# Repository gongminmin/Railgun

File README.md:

# Railgun

A railgun is a type of mass driver. It contains a pair of rails to accelerate a conductor projectile to a high velocity. This project is a design of a toy level railgun. We'd like to make it easy to implement, so people can build it as a hobby project.

NOTE: Please turn on git LFS when cloning this project.

## Design

The principle of our design, and a detailed introduction of subsystems are in [Design](Doc/Design.md)

## Disclaimer

A railgun is operated by **LETHALLY** high voltage and current. If you don't have enough knowledge and experiences on high voltage electric, please keep extreme cautions on insulation.

## Directories

* Circuit folder is the electric design of the system. The files can be open by [KiCad](https://kicad-pcb.org/)
* Doc folder contains some documents

## License

Railgun is distributed under the terms of MIT License. See [LICENSE](LICENSE) for details.

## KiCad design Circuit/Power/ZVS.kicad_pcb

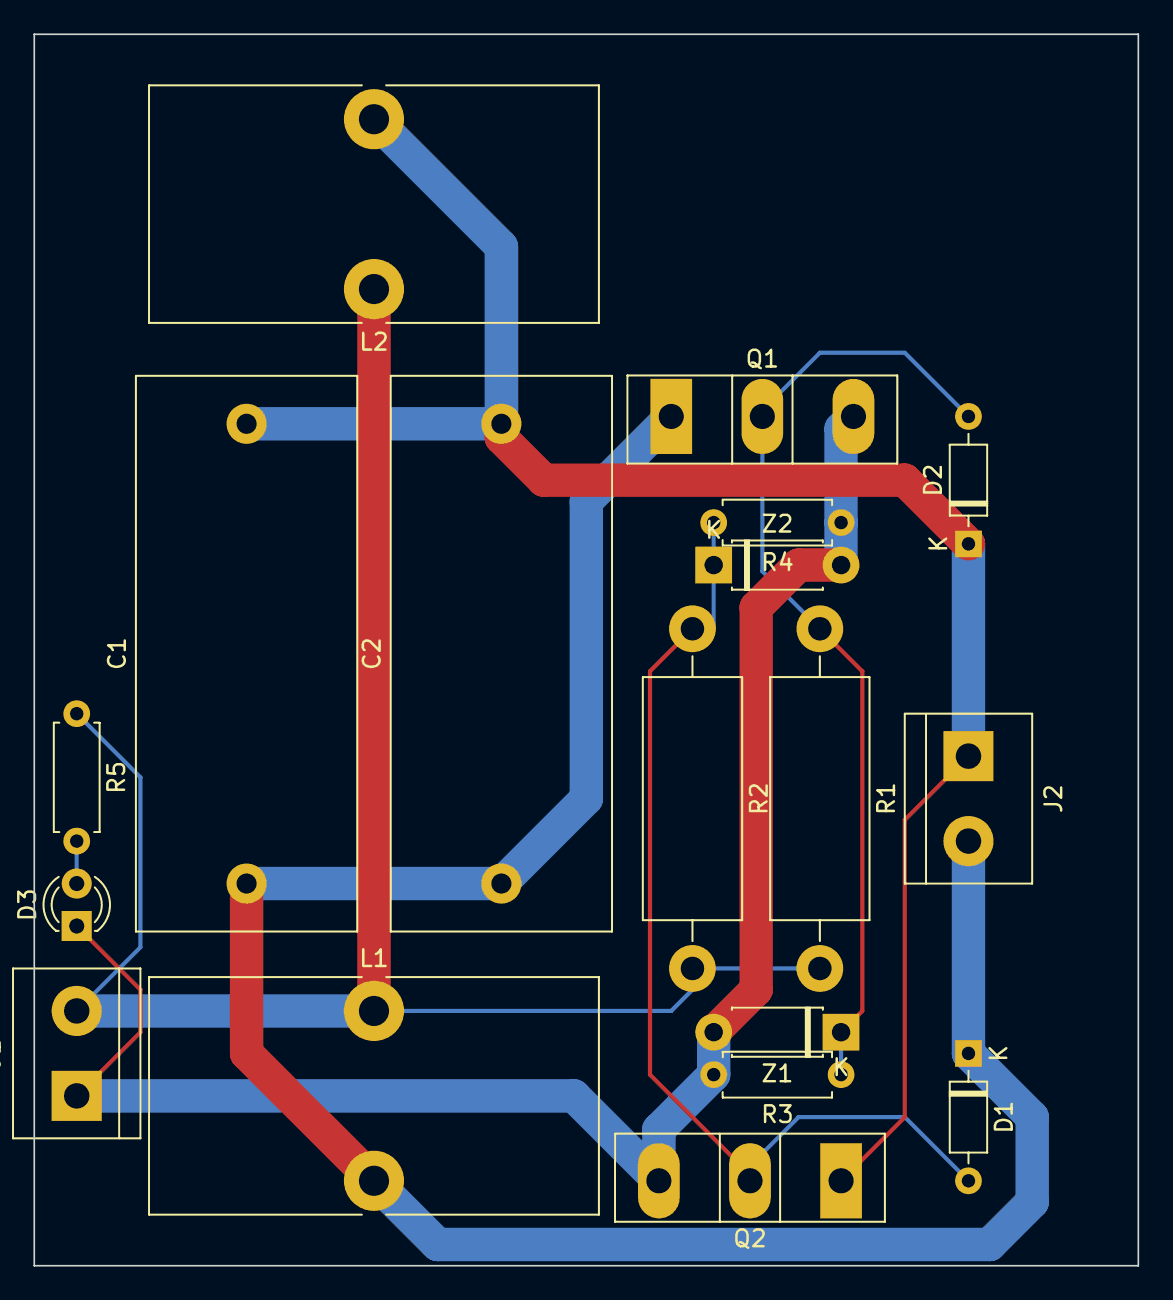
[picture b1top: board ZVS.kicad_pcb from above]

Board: 2 copper layers, 66.0 x 73.7 mm, 18 parts (0 on the bottom side), 7 nets.

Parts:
C1, C2: MKP 0.33uF; C_Rect_L33.0mm_W13.0mm_P27.50mm_MKS4
D1, D2: FR107; D_DO-35_SOD27_P7.62mm_Horizontal
D3: LED; LED_D3.0mm_FlatTop
J1: 12V DC in; TerminalBlock_bornier-2_P5.08mm
J2: Output; TerminalBlock_bornier-2_P5.08mm
L1, L2: 100uH; L_Toroid_Vertical_L26.7mm_W14.0mm_P10.16mm_Pulse_D
Q1, Q2: IRFP250; TO-247-3_Vertical
R1, R2: 470 2W; R_Axial_DIN0614_L14.3mm_D5.7mm_P20.32mm_Horizontal
R3, R4: 10K; R_Axial_DIN0207_L6.3mm_D2.5mm_P7.62mm_Horizontal
R5: 2.2K; R_Axial_DIN0207_L6.3mm_D2.5mm_P7.62mm_Horizontal
Z1, Z2: 1N4742; D_DO-41_SOD81_P7.62mm_Horizontal

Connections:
/DCInput+: J1.2, L1.1, L2.1, R1.2, R2.2, R5.1
/DCInput-: D3.1, J1.1, Q1.3, Q2.3, R3.2, R4.1, Z1.2, Z2.2
/Output+: C1.1, C2.1, D1.1, J2.2, L1.2, Q1.1
/Output-: C1.2, C2.2, D2.1, J2.1, L2.2, Q2.1
unnamed: D1.2, Q2.2, R2.1, R4.2, Z2.1
unnamed: D2.2, Q1.2, R1.1, R3.1, Z1.1
unnamed: D3.2, R5.2

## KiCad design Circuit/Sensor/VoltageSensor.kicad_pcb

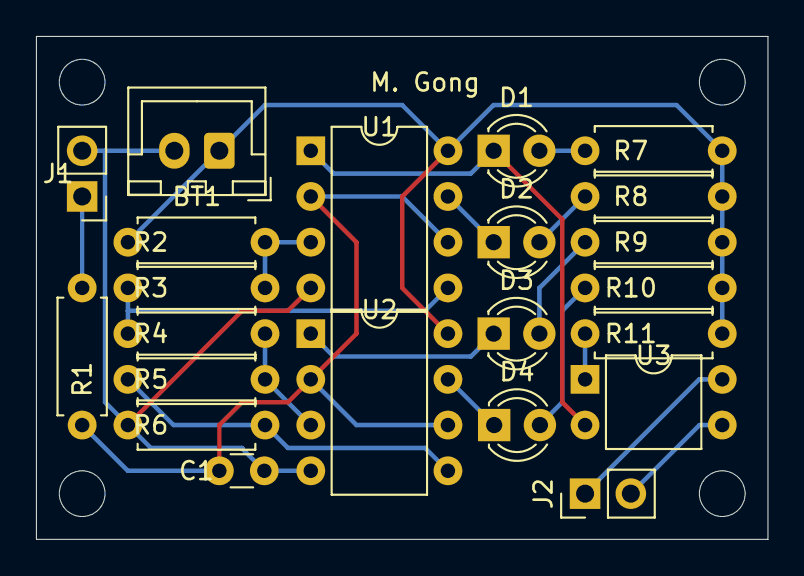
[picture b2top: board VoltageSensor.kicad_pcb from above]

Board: 2 copper layers, 40.6 x 27.9 mm, 22 parts (0 on the bottom side), 19 nets.

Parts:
BT1: 12V Battery; JST_XH_B2B-XH-A_1x02_P2.50mm_Vertical
C1: 0.1uF; C_Disc_D3.0mm_W1.6mm_P2.50mm
D1, D2, D3, D4: LED; LED_D3.0mm_FlatTop
J1: From Capacitor Bank; PinHeader_1x02_P2.54mm_Vertical
J2: To Control; PinHeader_1x02_P2.54mm_Vertical
R1, R11: 1K; R_Axial_DIN0207_L6.3mm_D2.5mm_P7.62mm_Horizontal
R2: 20K; R_Axial_DIN0207_L6.3mm_D2.5mm_P7.62mm_Horizontal
R3, R4, R5, R6: 4.7K; R_Axial_DIN0207_L6.3mm_D2.5mm_P7.62mm_Horizontal
R7, R8, R9, R10: 2.2K; R_Axial_DIN0207_L6.3mm_D2.5mm_P7.62mm_Horizontal
U1, U2: LM393; DIP-8_W7.62mm
U3: PC817; DIP-4_W7.62mm

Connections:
+12V: BT1.1, R2.2, R7.1, R8.1, R9.1, R10.1, R11.1, U1.8 (V+), U2.8 (V+)
/ControlGND: J2.2, U3.3
/ControlSignal: J2.1, U3.4
/Sensor6V: J1.1, R1.2
GND: BT1.2, C1.2, J1.2, R6.1, U1.4 (V-), U2.4 (V-)
unnamed: C1.1, R1.1, U1.2 (-), U1.6 (_), U2.2 (-), U2.6 (_)
unnamed: D1.1 (K), U1.1, U3.2
unnamed: D1.2 (A), R7.2
unnamed: D2.1 (K), U1.7
unnamed: D2.2 (A), R8.2
unnamed: D3.1 (K), U2.1
unnamed: D3.2 (A), R9.2
unnamed: D4.1 (K), U2.7
unnamed: D4.2 (A), R10.2
unnamed: R2.1, R3.2, U1.3 (+)
unnamed: R3.1, R4.2, U1.5 (+)
unnamed: R4.1, R5.2, U2.3 (+)
unnamed: R5.1, R6.2, U2.5 (+)
unnamed: R11.2, U3.1

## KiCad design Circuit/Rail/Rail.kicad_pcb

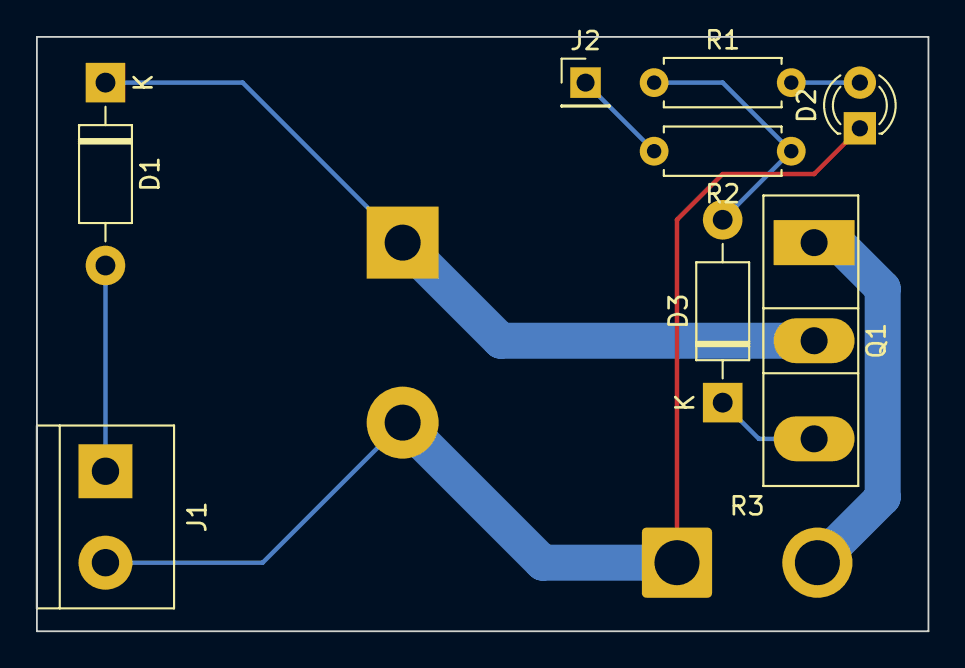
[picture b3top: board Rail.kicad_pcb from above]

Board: 2 copper layers, 49.5 x 33.0 mm, 10 parts (1 on the bottom side), 8 nets.

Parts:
C1: 1000uF 450V; CP_Radial_D30.0mm_P10.00mm_SnapIn
D1, D3: 1N4007; D_DO-41_SOD81_P10.16mm_Horizontal
D2: LED; LED_D3.0mm_FlatTop
J1: Coil Power; TerminalBlock_bornier-2_P5.08mm
J2: Trigger; PinHeader_1x01_P2.54mm_Vertical
Q1: 70PT12DS; TO-247-3_Vertical
R1, R2: 2.2K; R_Axial_DIN0207_L6.3mm_D2.5mm_P7.62mm_Horizontal
R3: Rail; SolderWire-2sqmm_1x02_P7.8mm_D2mm_OD3.9mm

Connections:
/RailPower+: D1.2 (A), J1.1
/TriggerPower: J2.1, R2.2
GND: C1.2, D2.1 (K), J1.2, R3.1
unnamed: C1.1, D1.1 (K), Q1.2 (A)
unnamed: D2.2 (A), R1.2
unnamed: D3.1 (K), Q1.3 (G)
unnamed: D3.2 (A), R1.1, R2.1
unnamed: Q1.1 (K), R3.2

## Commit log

2021-06-05 Init commit
2022-06-28 [Circuit] Update circuit files to KiCAD 6's
